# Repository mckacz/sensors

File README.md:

Simple wireless sensor system
=============================

As a part of home automation system for my house, I have designed a wireless sensors system that can continuously
monitor temperature, humidity, light and atmospheric pressure of multiple spots in the building.

This repository contains all elements required to build your own wireless sensor system based on ATmega328P, 
Raspberry PI and NRF24L01:

| Directory                          | Description                                            |
|------------------------------------|--------------------------------------------------------|
| [board](./board)                   | Schematic and PCB design of wireless sensor module     |
| [firmware](./firmware)             | Arduino-compatible firmware for wireless sensor module |
| [example-server](./example-server) | Simple wireless sensors server for Raspberry PI        | 

Case study
----------

As I mentioned, this wireless sensor system is a part of home automation system for my house.
At the moment, I have five wireless sensors connected to it. Each sensor module sends new readings in 16 seconds 
intervals and is powered by 3xAA rechargeable batteries - it is enough to power the module for over **2 months**. 
Power consumption is **~0.05 mA** in sleep mode and **20-30 mA** while measurements.  

**Cost of single module**

| Item                      | Price  | Note                                                                  |
|---------------------------|--------|-----------------------------------------------------------------------|
| PCB                       | $0.88  | ... if you order 20 PCB from EasyEDA (does not include shipping cost) |
| ATmega328P                | $1.23* |                                                                       |
| LD1117AV33                | $0.35* |                                                                       |
| NRF24L01+                 | $0.75* |                                                                       |
| HTU21D                    | $2.40* |                                                                       |
| TSL2561                   | $1.50* |                                                                       |
| BMP180                    | $2.20* |                                                                       |
| Other parts               | $0.50* | Resistors, transistor, sockets                                        |

Fully featured version: **$9.81**  
Temperature + humidity + light: **$7.61**  
Temperature + humidity: **$6.11**

Sums do not include cost of power supply. 

*) Prices from aliexpress.com (2016-12-04).

License
-------

[MIT](./LICENSE)

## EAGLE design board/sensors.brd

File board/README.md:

Wireless sensor module board
============================

This directory contains schematic and PCB design for single wireless sensor module in [EAGLE](https://cadsoft.io/) 
format. Board design is also available on [EasyEDA](https://easyeda.com/maciej/sensors-387a7c4150d841bbb06d5350ea664e67).  

**Features**:
 * small dimensions - 55x45mm
 * low power consumption - ~40mA during measurement and ~40µA (0.04mA) in standby
 * supports standard BMP180, HTU21D and TSL2561 breakout boards - min. one is required, but all can be installed at same time 
 * input voltage from 3 to 5.5V 
 * low cost
 * open source [firmware](../firmware) 

Part list
---------

| PCB ID | Part name            | Qty | Description                     |
|--------|----------------------|-----|---------------------------------|
| U1     | ATmega328P (DIL28)   |  1  | microcontroller                 |
| U2     | LD1117AV33 (TO220)   |  1  | voltage regulator               |
| U3     | NRF24L01+            |  1  | radio module                    |
| U4     | HTU21D (breakboard)  |  1  | temperature and humidity sensor | 
| U5/U6* | TSL2561 (breakboard) |  1  | luminescence sensor             | 
| U7     | BMP180 (breakboard)  |  1  | barometer sensor                |
| R1, R2 | resistor 10k         |  2  | resistor                        |
| Q1     | BC337-40             |  1  | NPN transistor                  | 
|        | pinhead 1x2          |  1  | pin header connector            | 
|        | pinhead 1x3          |  1  | pin header connector            | 
|        | pinhead 1x4          |  1  | pin header connector            | 
|        | pinhead 2x4          |  1  | pin header connector            | 
|        | pinhead 1x5          |  3  | pin header connector            | 
|        | DIL28 socket         |  1  | socket for ATmega328P           | 

*) There are two TSL2561 connectors (with different pin order) on the board, 
   but only one TSL2561 can be used at same time. 
 
Top layer
---------

Bottom layer
------------

Assembled board
---------------

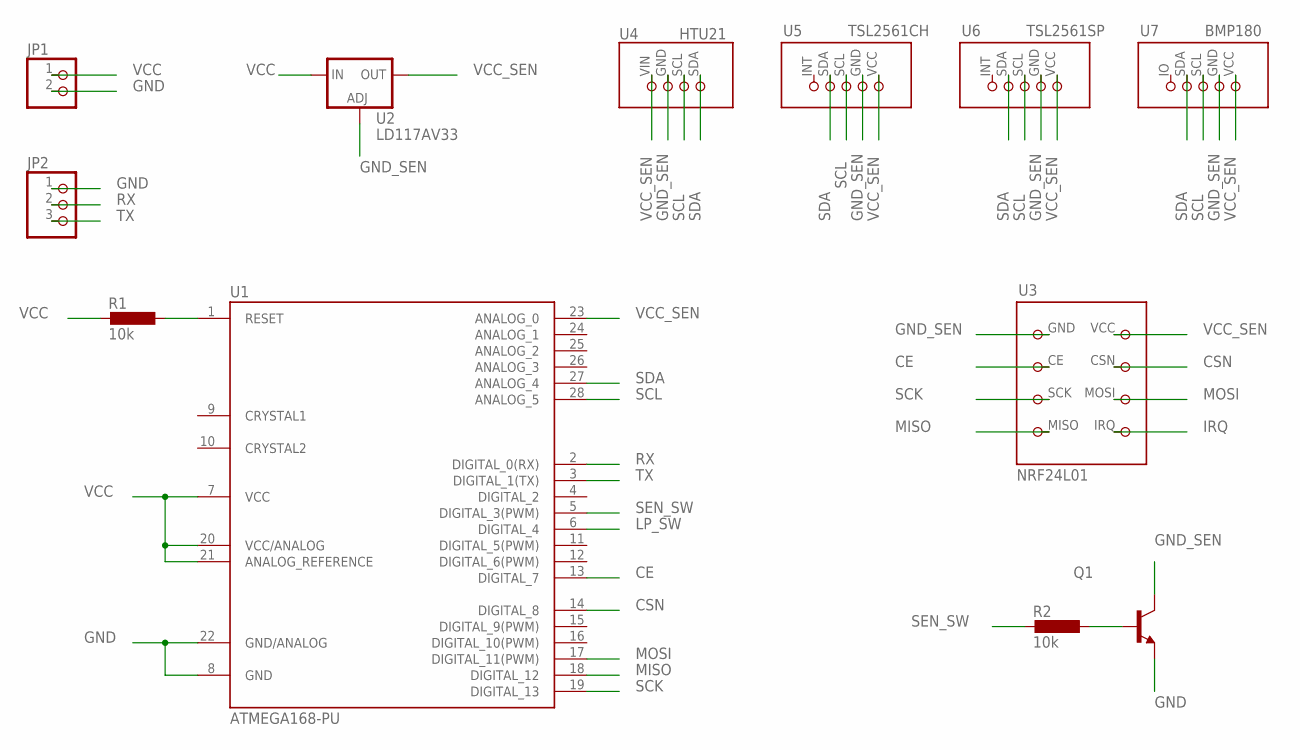
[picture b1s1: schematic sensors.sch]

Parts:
JP1: PINHD-1X2; 1X02
JP2: PINHD-1X3; 1X03
Q1: -NPN-TO92-EBC; TO92-EBC
R1, R2: 10k; 0207/10
U1: ATMEGA168-PU; DIL28-3
U2: LD117AV33; TO220L1
U3: NRF24L01
U4: HTU21
U5: TSL2561CH; TSL2561-CH
U6: TSL2561SP; TSL2561-SP
U7: BMP180

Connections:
CE: U1.13 (DIGITAL_7), U3.CE
CSN: U1.14 (DIGITAL_8), U3.CSN
GND: JP1.2, JP2.1, Q1.E, U1.8 (GND), U1.22 (GND/ANALOG)
GND_SEN: Q1.C, U2.1 (ADJ), U3.GND, U4.GND, U5.GND, U6.GND, U7.GND
IRQ: U3.IRQ
LP_SW: U1.6 (DIGITAL_4)
MISO: U1.18 (DIGITAL_12), U3.MISO
MOSI: U1.17 (DIGITAL_11(PWM)), U3.MOSI
unnamed: R1.1, U1.1 (RESET)
unnamed: Q1.B, R2.1
RX: JP2.2, U1.2 (DIGITAL_0(RX))
SCK: U1.19 (DIGITAL_13), U3.SCK
SCL: U1.28 (ANALOG_5), U4.SCL, U5.SCL, U6.SCL, U7.SCL
SDA: U1.27 (ANALOG_4), U4.SDA, U5.SDA, U6.SDA, U7.SDA
SEN_SW: R2.2, U1.5 (DIGITAL_3(PWM))
TX: JP2.3, U1.3 (DIGITAL_1(TX))
VCC: JP1.1, R1.2, U1.7 (VCC), U1.20 (VCC/ANALOG), U1.21 (ANALOG_REFERENCE), U2.3 (IN)
VCC_SEN: U1.23 (ANALOG_0), U2.2 (OUT), U3.VCC, U4.VIN, U5.VCC, U6.VCC, U7.VCC

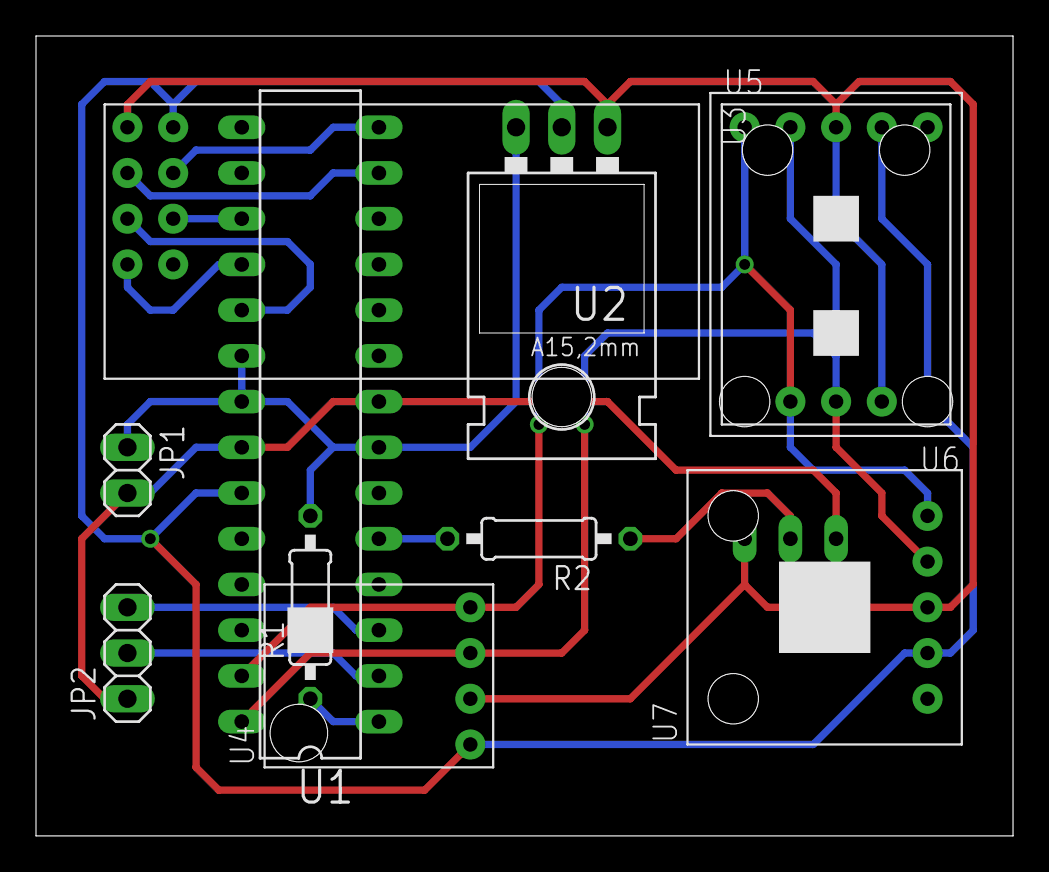
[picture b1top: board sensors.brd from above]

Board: 2 copper layers, 54.3 x 44.4 mm, 12 parts (1 on the bottom side), 16 nets.

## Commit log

2016-11-27 Import to Git
2016-11-27 gitignore
2016-11-27 Cleanup code
2016-11-27 Include python cache files in gitignore.
2016-12-01 License
2016-12-01 Board and Firmare READMEs
2016-12-02 Status bitmasks fix.
2016-12-02 Cleanup in server-example
2016-12-02 Firmware README
2016-12-04 Example server README and minor modifications
2016-12-04 Main README, screenshots and minor fixes.
